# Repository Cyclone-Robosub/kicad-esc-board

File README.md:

# kicad-esc-board
PCB for mounting and cooling ESCs in a small footprint.

# Use
1. Open the `.kicad_pro` file in KiCAD 10.0 or later.
2. Add the custom symbols library in `Preferences` -> `Manage Symbol Libraries` -> `Project Specific Libraries` -> Folder Icon Dropdown -> `KiCAD (.kicad_sym)`. When the folder dialog opens, navigate to `.../kicad-esc-board/Resources` and select `esc_board_custom_symbols.kicad_sym`. Click `OK` to save and exit.
3. Add the footprint libraries in `Footprint Editor` -> `Preferences` -> `Manage Footprint Libraries` -> `Project Specifc Libraries` -> Folder Icon Dropdown -> 'KiCAD (folder with .kicad_mod files)`. When the folder dialog opens, navigate to `.../kicad-esc-board/Resources` and select the `esc_board_custom_footprints.pretty' folder. Click `OK` to save and exit.

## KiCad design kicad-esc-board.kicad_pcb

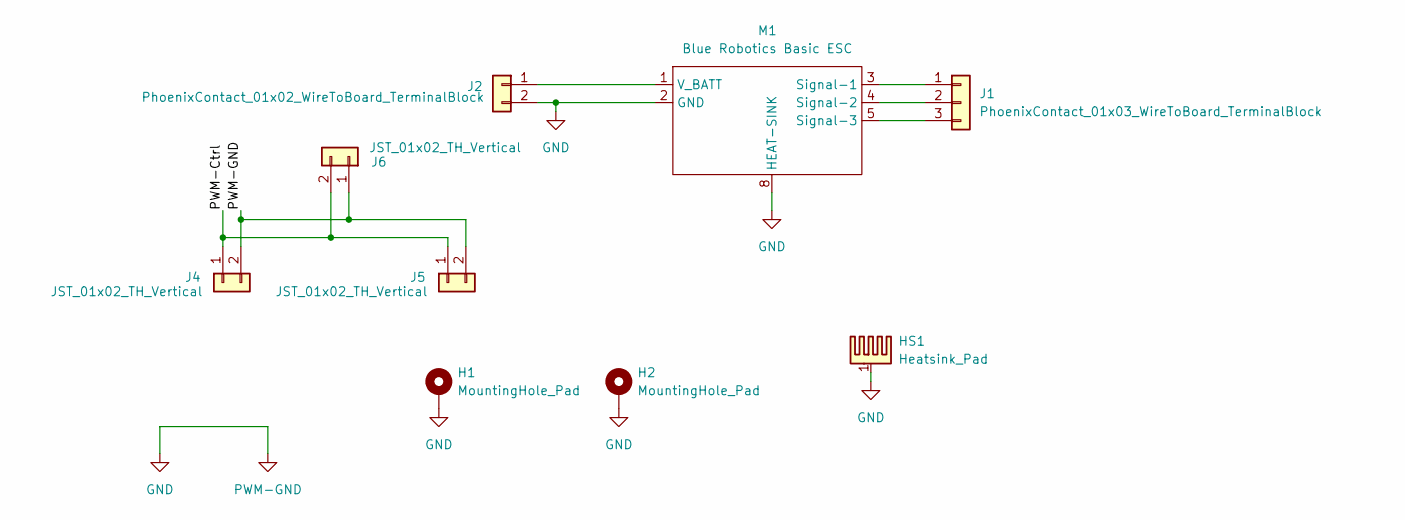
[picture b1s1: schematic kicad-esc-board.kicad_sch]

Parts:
H1, H2: MountingHole_Pad; MountingHole_3.2mm_M3_Pad
HS1: Heatsink_Pad; ESC_HeatSink
J1: PhoenixContact_01x03_WireToBoard_TerminalBlock; CONN_1017492
J2: PhoenixContact_01x02_WireToBoard_TerminalBlock; CONN_1017491
J4, J5: JST_01x02_TH_Vertical; JST_B2B-PH-K-S
J6: JST_01x02_TH_Vertical; PinHeader_1x02_P2.00mm_Vertical
M1: Blue Robotics Basic ESC; BlueRobotics_ESC_Basic

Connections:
/PWM-Ctrl: J4.1, J5.1, J6.2
GND: H1.1 (1_1), H2.1 (1_1), HS1.1, J2.2, J4.2, J5.2, J6.1, M1.2 (GND), M1.8 (HEAT-SINK)
unnamed: J1.1, M1.3 (Signal-1)
unnamed: J1.2, M1.4 (Signal-2)
unnamed: J1.3, J1.4, M1.5 (Signal-3)
unnamed: J2.1, M1.1 (V_BATT)

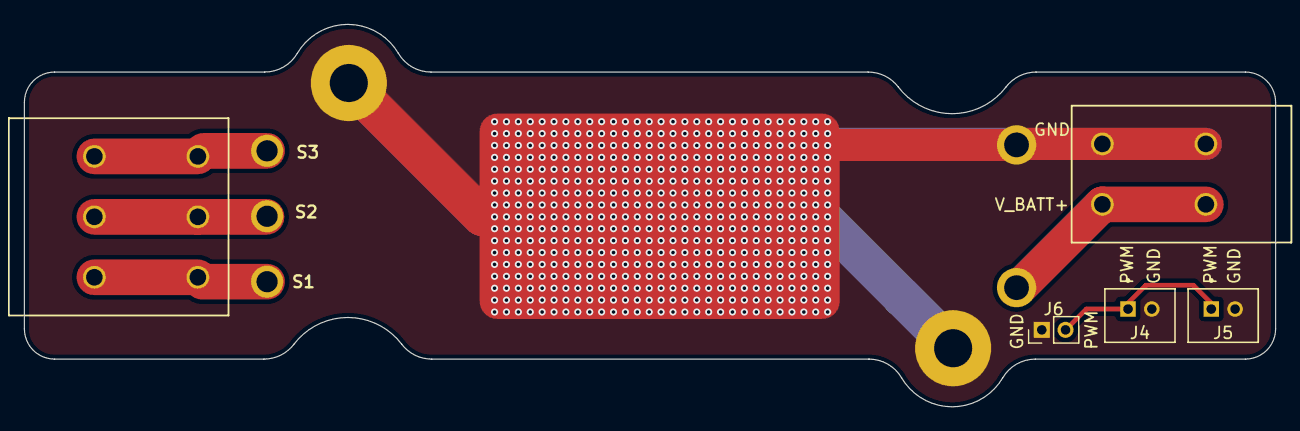
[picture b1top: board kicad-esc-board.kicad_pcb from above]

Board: 2 copper layers, 105.2 x 32.1 mm, 9 parts (1 on the bottom side), 6 nets.
